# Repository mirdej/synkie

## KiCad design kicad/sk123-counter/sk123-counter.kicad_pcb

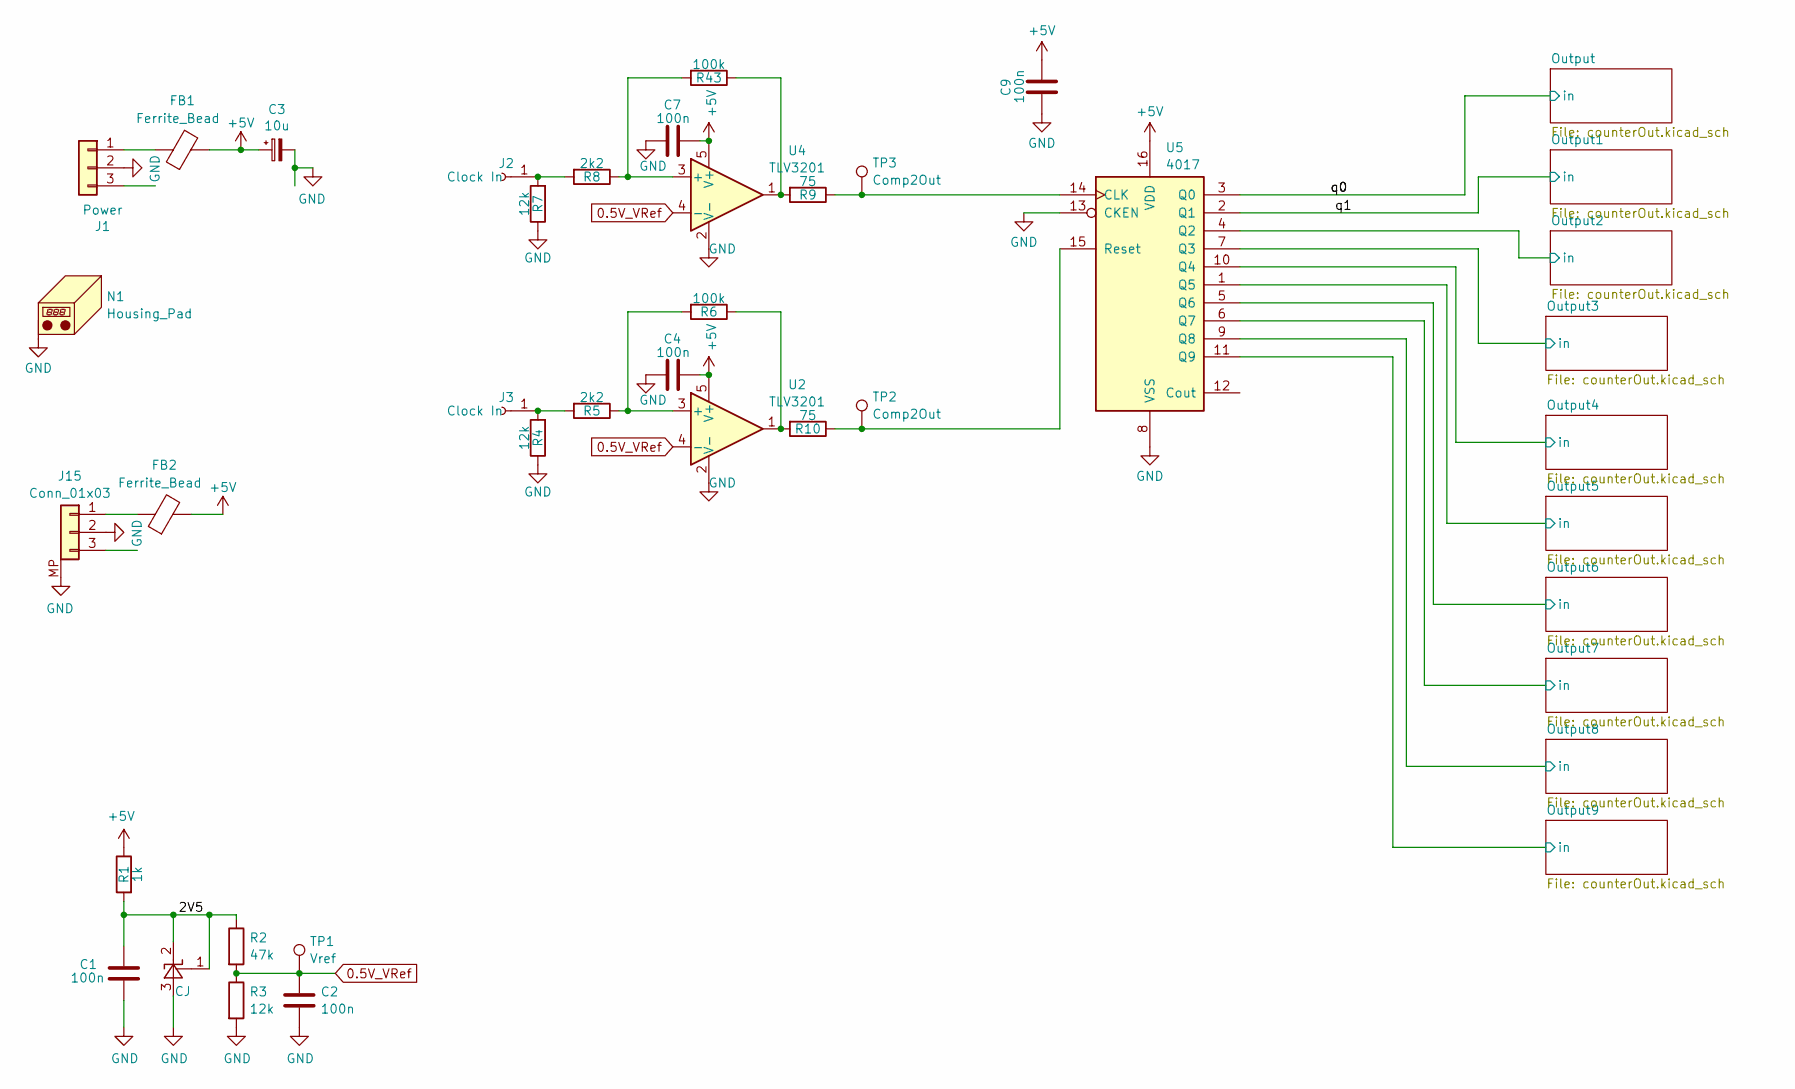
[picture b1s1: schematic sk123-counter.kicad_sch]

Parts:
C1, C2, C4, C7, C9: 100n; C_0603_1608Metric; LCSC C14663
C3: 10u; C_0805_2012Metric; LCSC C15850
FB1, FB2: Ferrite_Bead; L_0805_2012Metric; LCSC C1017
J1: Power; Molex_KK-254_AE-6410-03A_1x03_P2.54mm_Vertical_SMD
J2, J3: Clock In; Banana2mm-Löthülse
J15: Conn_01x03; Molex_PicoBlade_53398-0371_1x03-1MP_P1.25mm_Vertical; LCSC C293633
N1: Housing_Pad; Frontplate_20mm
R1: 1k; R_0603_1608Metric; LCSC C21190
R2: 47k; R_0603_1608Metric; LCSC C25819
R3, R4, R7: 12k; R_0603_1608Metric; LCSC C22790
R5, R8: 2k2; R_0603_1608Metric; LCSC C4190
R6, R43: 100k; R_0603_1608Metric; LCSC C25803
R9, R10: 75; R_0603_1608Metric; LCSC C4275
TP1: Vref; TestPoint_Pad_D1.0mm
TP2, TP3: Comp2Out; TestPoint_Pad_D1.0mm
U1: CJ; SOT-23; LCSC C3113
U2, U4: TLV3201; SOT-23-5; LCSC C105188
U5: 4017; SO-16_3.9x9.9mm_P1.27mm; LCSC C546952

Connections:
0.5V_VRef: C2.1, R2.2, R3.1, TP1.1 (1_1), U2.4 (-), U4.4 (-)
+5V: C3.1, C4.2, C7.2, C9.2, FB1.2, FB2.2, R1.1, U2.5 (V+), U4.5 (V+), U5.16 (VDD); also elsewhere on the board
/2V5: C1.1, R1.2, R2.1, U1.1 (R), U1.2 (K)
/Output2/in: U5.4 (Q2); also elsewhere on the board
/Output3/in: U5.7 (Q3); also elsewhere on the board
/Output4/in: U5.10 (Q4); also elsewhere on the board
/Output5/in: U5.1 (Q5); also elsewhere on the board
/Output6/in: U5.5 (Q6); also elsewhere on the board
/Output7/in: U5.6 (Q7); also elsewhere on the board
/Output8/in: U5.9 (Q8); also elsewhere on the board
/Output9/in: U5.11 (Q9); also elsewhere on the board
/Output/in: U5.3 (Q0); also elsewhere on the board
/q1: U5.2 (Q1); also elsewhere on the board
GND: C1.2, C2.2, C3.2, C4.1, C7.1, C9.1, J1.2, J15.2, J15.MP, N1.1 (PAD_1), R3.2, R4.1, R7.1, U1.3 (A), U2.2 (V-), U4.2 (V-), U5.8 (VSS), U5.13 (CKEN); also elsewhere on the board
unnamed: FB1.1, J1.1
unnamed: J2.1 (Pin_1_1), R7.2, R8.2
unnamed: J3.1 (Pin_1_1), R4.2, R5.2
unnamed: FB2.1, J15.1
unnamed: R6.1, R10.2, U2.1
unnamed: R9.2, R43.1, U4.1
unnamed: R5.1, R6.2, U2.3 (+)
unnamed: R8.1, R43.2, U4.3 (+)
unnamed: R9.1, TP3.1 (1_1), U5.14 (CLK)
unnamed: R10.1, TP2.1 (1_1), U5.15 (Reset)

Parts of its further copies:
R18: 2k2; R_0603_1608Metric; LCSC C4190

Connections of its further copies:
unnamed 15: R18.1; also elsewhere on the board
unnamed 41: R18.2; also elsewhere on the board

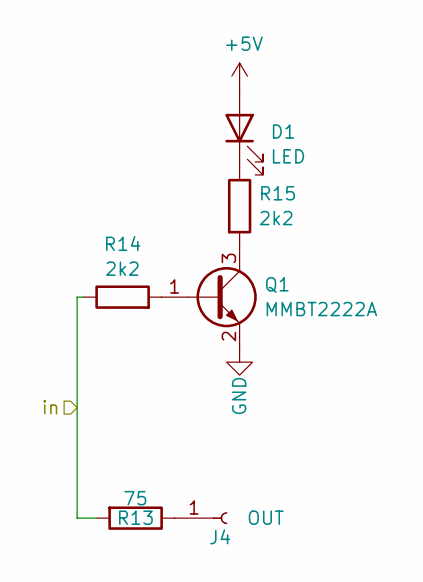
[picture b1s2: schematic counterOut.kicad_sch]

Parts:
D1: LED; LED_1206_3216Metric_ReverseMount_Hole1.8x2.4mm; LCSC C125108
J4: OUT; Banana2mm-Löthülse
Q1: MMBT2222A; SOT-23; LCSC C8512
R13: 75; R_0603_1608Metric; LCSC C4275
R14, R15: 2k2; R_0603_1608Metric; LCSC C4190

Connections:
+5V: D1.2 (A); also elsewhere on the board
/Output/in: R13.2, R14.1; also elsewhere on the board
GND: Q1.2 (E); also elsewhere on the board
unnamed: D1.1 (K), R15.1
unnamed: J4.1 (Pin_1_1), R13.1
unnamed: Q1.1 (B), R14.2
unnamed: Q1.3 (C), R15.2

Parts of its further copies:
D2, D3, D4, D5, D6, D7, D8, D9, D10: LED; LED_1206_3216Metric_ReverseMount_Hole1.8x2.4mm; LCSC C125108
J5, J6, J7, J8, J9, J10, J11, J12, J13: OUT; Banana2mm-Löthülse
Q2, Q3, Q4, Q5, Q6, Q7, Q8, Q9, Q10: MMBT2222A; SOT-23; LCSC C8512
R16, R18, R19, R21, R22, R24, R25, R27, R28, R30, R31, R33, R34, R36, R37, R39, R40, R42: 2k2; R_0603_1608Metric; LCSC C4190
R17, R20, R23, R26, R29, R32, R35, R38, R41: 75; R_0603_1608Metric; LCSC C4275

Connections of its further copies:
+5V: D2.2 (A), D3.2 (A), D4.2 (A), D5.2 (A), D6.2 (A), D7.2 (A), D8.2 (A), D9.2 (A), D10.2 (A); also elsewhere on the board
/Output2/in: R22.1, R23.2; also elsewhere on the board
/Output3/in: R19.1, R20.2; also elsewhere on the board
/Output4/in: R25.1, R26.2; also elsewhere on the board
/Output5/in: R28.1, R29.2; also elsewhere on the board
/Output6/in: R31.1, R32.2; also elsewhere on the board
/Output7/in: R34.1, R35.2; also elsewhere on the board
/Output8/in: R37.1, R38.2; also elsewhere on the board
/Output9/in: R40.1, R41.2; also elsewhere on the board
/q1: R16.1, R17.2; also elsewhere on the board
GND: Q2.2 (E), Q3.2 (E), Q4.2 (E), Q5.2 (E), Q6.2 (E), Q7.2 (E), Q8.2 (E), Q9.2 (E), Q10.2 (E); also elsewhere on the board
unnamed: D2.1 (K), R18.1
unnamed: D3.1 (K), R21.1
unnamed: D4.1 (K), R24.1
unnamed: D5.1 (K), R27.1
unnamed: D6.1 (K), R30.1
unnamed: D7.1 (K), R33.1
unnamed: D8.1 (K), R36.1
unnamed: D9.1 (K), R39.1
unnamed: D10.1 (K), R42.1
unnamed: J5.1 (Pin_1_1), R17.1
unnamed: J6.1 (Pin_1_1), R20.1
unnamed: J7.1 (Pin_1_1), R23.1
unnamed: J8.1 (Pin_1_1), R26.1
unnamed: J9.1 (Pin_1_1), R29.1
unnamed: J10.1 (Pin_1_1), R32.1
unnamed: J11.1 (Pin_1_1), R35.1
unnamed: J12.1 (Pin_1_1), R38.1
unnamed: J13.1 (Pin_1_1), R41.1
unnamed: Q2.1 (B), R16.2
unnamed: Q2.3 (C), R18.2
unnamed: Q3.1 (B), R19.2
unnamed: Q3.3 (C), R21.2
unnamed: Q4.1 (B), R22.2
unnamed: Q4.3 (C), R24.2
unnamed: Q5.1 (B), R25.2
unnamed: Q5.3 (C), R27.2
unnamed: Q6.1 (B), R28.2
unnamed: Q6.3 (C), R30.2
unnamed: Q7.1 (B), R31.2
unnamed: Q7.3 (C), R33.2
unnamed: Q8.1 (B), R34.2
unnamed: Q8.3 (C), R36.2
unnamed: Q9.1 (B), R37.2
unnamed: Q9.3 (C), R39.2
unnamed: Q10.1 (B), R40.2
unnamed: Q10.3 (C), R42.2

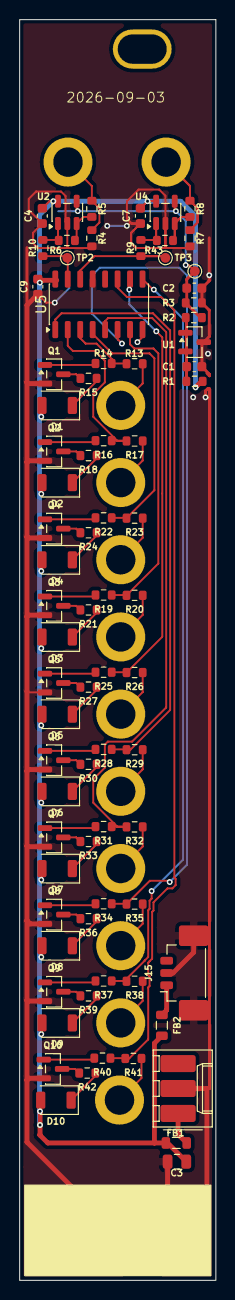
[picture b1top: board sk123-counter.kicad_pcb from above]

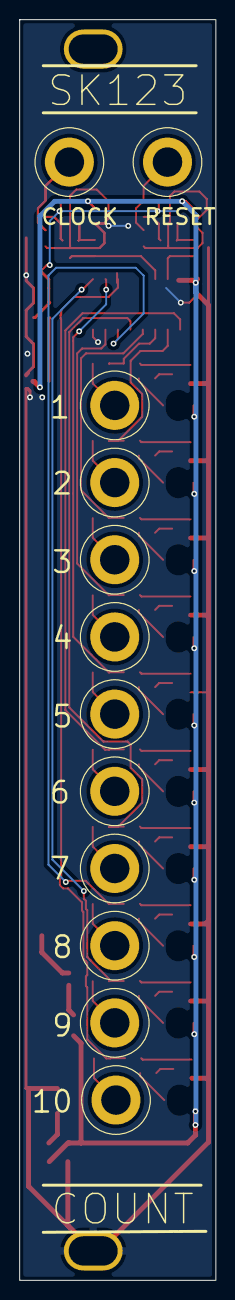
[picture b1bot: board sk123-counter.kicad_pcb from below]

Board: 2 copper layers, 20.0 x 128.5 mm, 91 parts (13 on the bottom side), 64 nets.

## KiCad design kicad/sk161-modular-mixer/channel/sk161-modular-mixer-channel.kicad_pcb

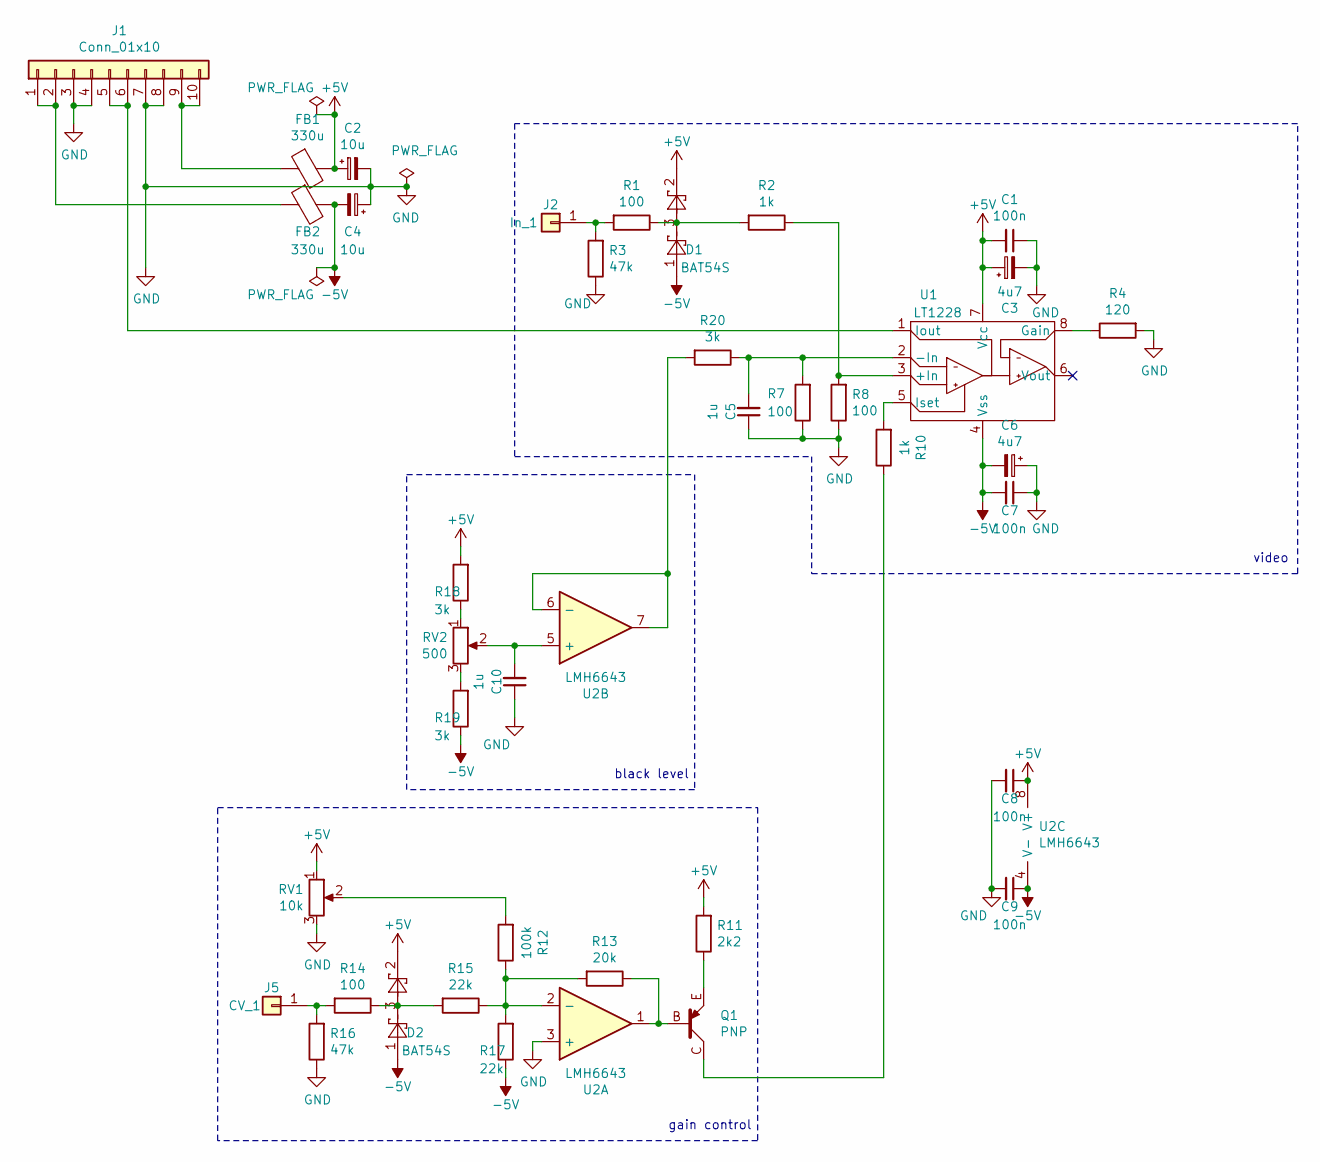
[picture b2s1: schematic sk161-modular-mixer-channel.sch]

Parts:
C1, C7, C8, C9: 100n; C_0603_1608Metric_Pad1.05x0.95mm_HandSolder
C2, C4: 10u; CP_EIA-3528-21_Kemet-B_Pad1.50x2.35mm_HandSolder
C3, C6: 4u7; CP_EIA-3528-21_Kemet-B_Pad1.50x2.35mm_HandSolder
C5, C10: 1u; C_0603_1608Metric_Pad1.05x0.95mm_HandSolder
D1, D2: BAT54S; SOT-23
FB1, FB2: 330u; L_0805_2012Metric_Pad1.15x1.40mm_HandSolder
J1: Conn_01x10; IDC-Header_2x05_P2.54mm_Vertical
J2: In_1; Solderpad_1mm
J5: CV_1; Solderpad_1mm
Q1: PNP; SOT-23_BEC
R1, R7, R8, R14: 100; R_0805_2012Metric_Pad1.15x1.40mm_HandSolder
R2, R10: 1k; R_0805_2012Metric_Pad1.15x1.40mm_HandSolder
R3, R16: 47k; R_0805_2012Metric_Pad1.15x1.40mm_HandSolder
R4: 120; R_0805_2012Metric_Pad1.15x1.40mm_HandSolder
R11: 2k2; R_0805_2012Metric_Pad1.15x1.40mm_HandSolder
R12: 100k; R_0805_2012Metric_Pad1.15x1.40mm_HandSolder
R13: 20k; R_0805_2012Metric_Pad1.15x1.40mm_HandSolder
R15, R17: 22k; R_0805_2012Metric_Pad1.15x1.40mm_HandSolder
R18, R19, R20: 3k; R_0805_2012Metric_Pad1.15x1.40mm_HandSolder
RV1: 10k; Potentiometer_Alps_RS6011xP_Slide
RV2: 500; Potentiometer_Bourns_3296Y_Vertical
U1: LT1228; SOIC-8_3.9x4.9mm_P1.27mm
U2: LMH6643; SOIC-8_3.9x4.9mm_P1.27mm

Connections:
+5V: C1.2, C2.1, C3.1, C8.1, D1.2, D2.2, FB1.2, R11.2, R18.2, RV1.1, U1.7 (Vcc), U2.8 (V+)
-5V: C4.2, C6.2, C7.2, C9.1, D1.1, D2.1, FB2.2, R17.1, R19.1, U1.4 (Vss), U2.4 (V-)
GND: C1.1, C2.2, C3.2, C4.1, C5.1, C6.1, C7.1, C8.2, C9.2, C10.1, J1.3, J1.4, J1.7, J1.8, R3.1, R4.2, R7.1, R8.1, R16.1, RV1.3, RV1.4, RV1.5, U2.3 (+)
unnamed: C5.2, R7.2, R20.1, U1.2 (-In)
unnamed: C10.2, RV2.2, U2.5 (+)
unnamed: D1.3, R1.1, R2.2
unnamed: D2.3, R14.1, R15.2
unnamed: FB1.1, J1.9, J1.10
unnamed: FB2.1, J1.1, J1.2
unnamed: J1.5, J1.6, U1.1 (Iout)
unnamed: J2.1, R1.2, R3.2
unnamed: J5.1, R14.2, R16.2
unnamed: Q1.B, R13.1, U2.1
unnamed: Q1.C, R10.1
unnamed: Q1.E, R11.1
unnamed: R2.1, R8.2, U1.3 (+In)
unnamed: R4.1, U1.8 (Gain)
unnamed: R10.2, U1.5 (Iset)
unnamed: R12.1, R13.2, R15.1, R17.2, U2.2 (-)
unnamed: R12.2, RV1.2
unnamed: R18.1, RV2.1
unnamed: R19.2, RV2.3
unnamed: R20.2, U2.6 (-), U2.7

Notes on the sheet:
black level
gain control
video

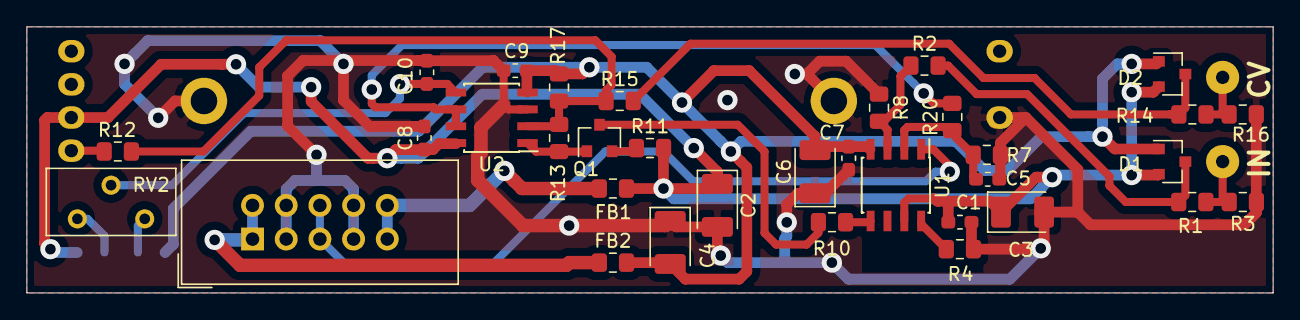
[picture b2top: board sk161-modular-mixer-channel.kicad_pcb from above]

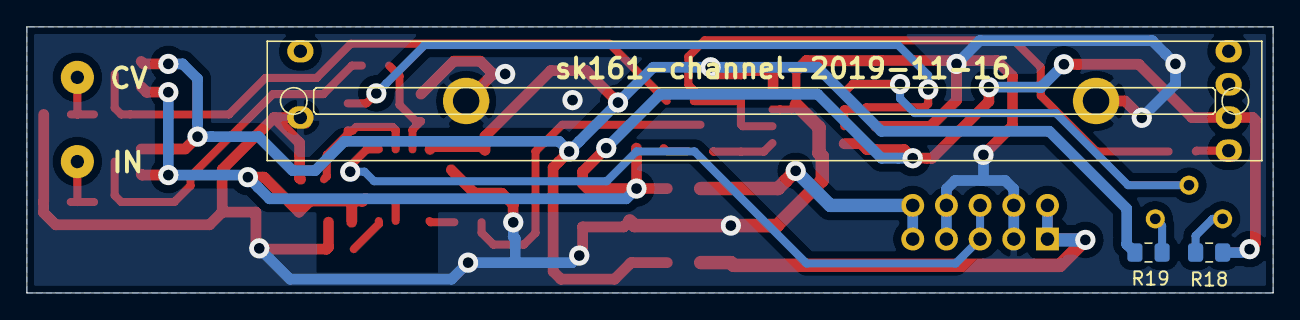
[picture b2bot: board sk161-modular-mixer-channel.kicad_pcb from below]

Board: 2 copper layers, 94.0 x 20.1 mm, 39 parts (3 on the bottom side), 23 nets.

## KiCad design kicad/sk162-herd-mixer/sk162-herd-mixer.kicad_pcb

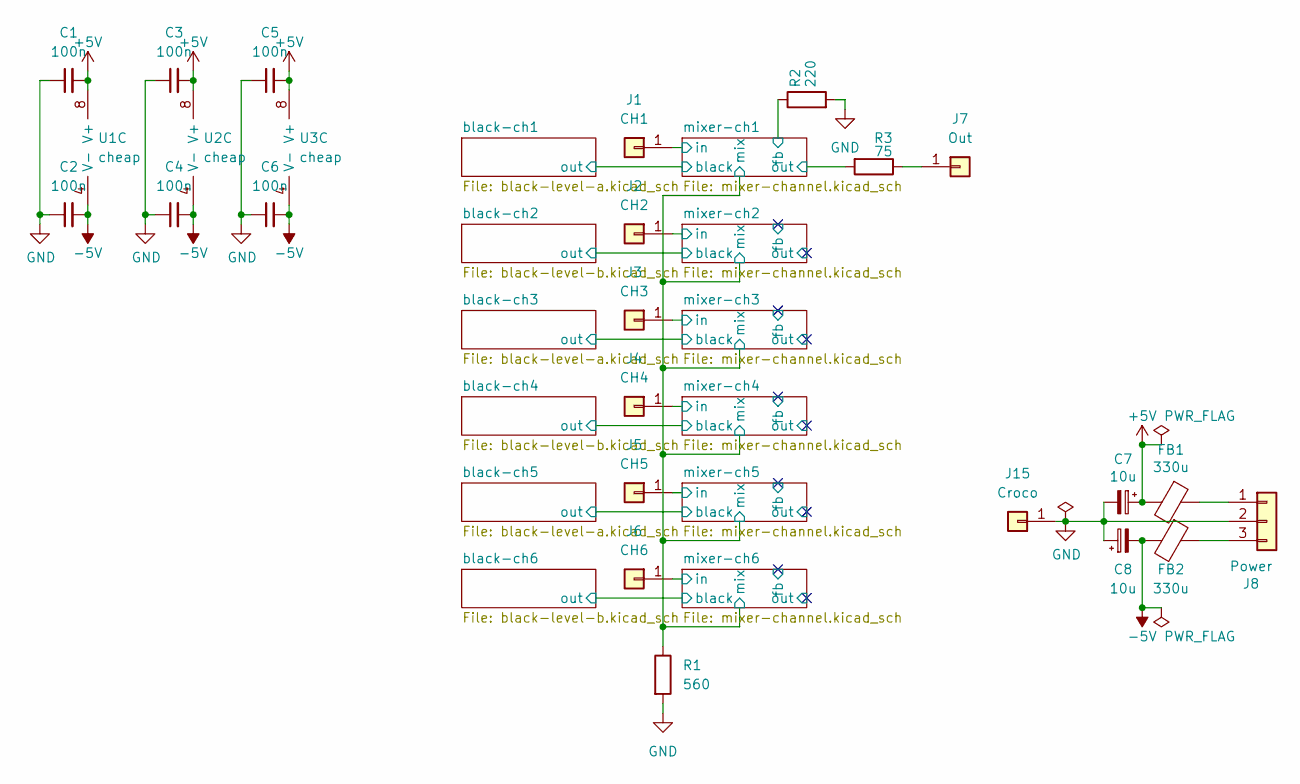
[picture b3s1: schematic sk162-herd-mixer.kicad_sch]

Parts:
C1, C2, C3, C4, C5, C6: 100n; C_0603_1608Metric_Pad1.05x0.95mm_HandSolder
C7, C8: 10u; C_0805_2012Metric_Pad1.15x1.40mm_HandSolder
FB1, FB2: 330u; L_0805_2012Metric_Pad1.15x1.40mm_HandSolder
J1: CH1; Solderpad-SYNKIEPAD-2mm
J2: CH2; Solderpad-SYNKIEPAD-2mm
J3: CH3; Solderpad-SYNKIEPAD-2mm
J4: CH4; Solderpad-SYNKIEPAD-2mm
J5: CH5; Solderpad-SYNKIEPAD-2mm
J6: CH6; Solderpad-SYNKIEPAD-2mm
J7: Out; Solderpad-SYNKIEPAD-2mm
J8: Power; Molex_KK-254_AE-6410-03A_1x03_P2.54mm_Vertical
J15: Croco; CrocodileGroundPad
R1: 560; R_0805_2012Metric_Pad1.15x1.40mm_HandSolder
R2: 220; R_0805_2012Metric_Pad1.15x1.40mm_HandSolder
R3: 75; R_0805_2012Metric_Pad1.15x1.40mm_HandSolder
U1, U2, U3: cheap; SOIC-8_3.9x4.9mm_P1.27mm

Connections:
+5V: C1.2, C3.2, C5.2, C7.1, FB1.2, U1.8 (V+), U2.8 (V+), U3.8 (V+); also elsewhere on the board
-5V: C2.2, C4.2, C6.2, C8.2, FB2.2, U1.4 (V-), U2.4 (V-), U3.4 (V-); also elsewhere on the board
/mixer-ch1/fb: R2.1; also elsewhere on the board
/mixer-ch1/in: J1.1; also elsewhere on the board
/mixer-ch1/mix: R1.1; also elsewhere on the board
/mixer-ch1/out: R3.2; also elsewhere on the board
/mixer-ch2/in: J2.1; also elsewhere on the board
/mixer-ch3/in: J3.1; also elsewhere on the board
/mixer-ch4/in: J4.1; also elsewhere on the board
/mixer-ch5/in: J5.1; also elsewhere on the board
/mixer-ch6/in: J6.1; also elsewhere on the board
GND: C1.1, C2.1, C3.1, C4.1, C5.1, C6.1, C7.2, C8.1, J8.2, J15.1, R1.2, R2.2; also elsewhere on the board
unnamed: J7.1, R3.1
unnamed: FB1.1, J8.1
unnamed: FB2.1, J8.3

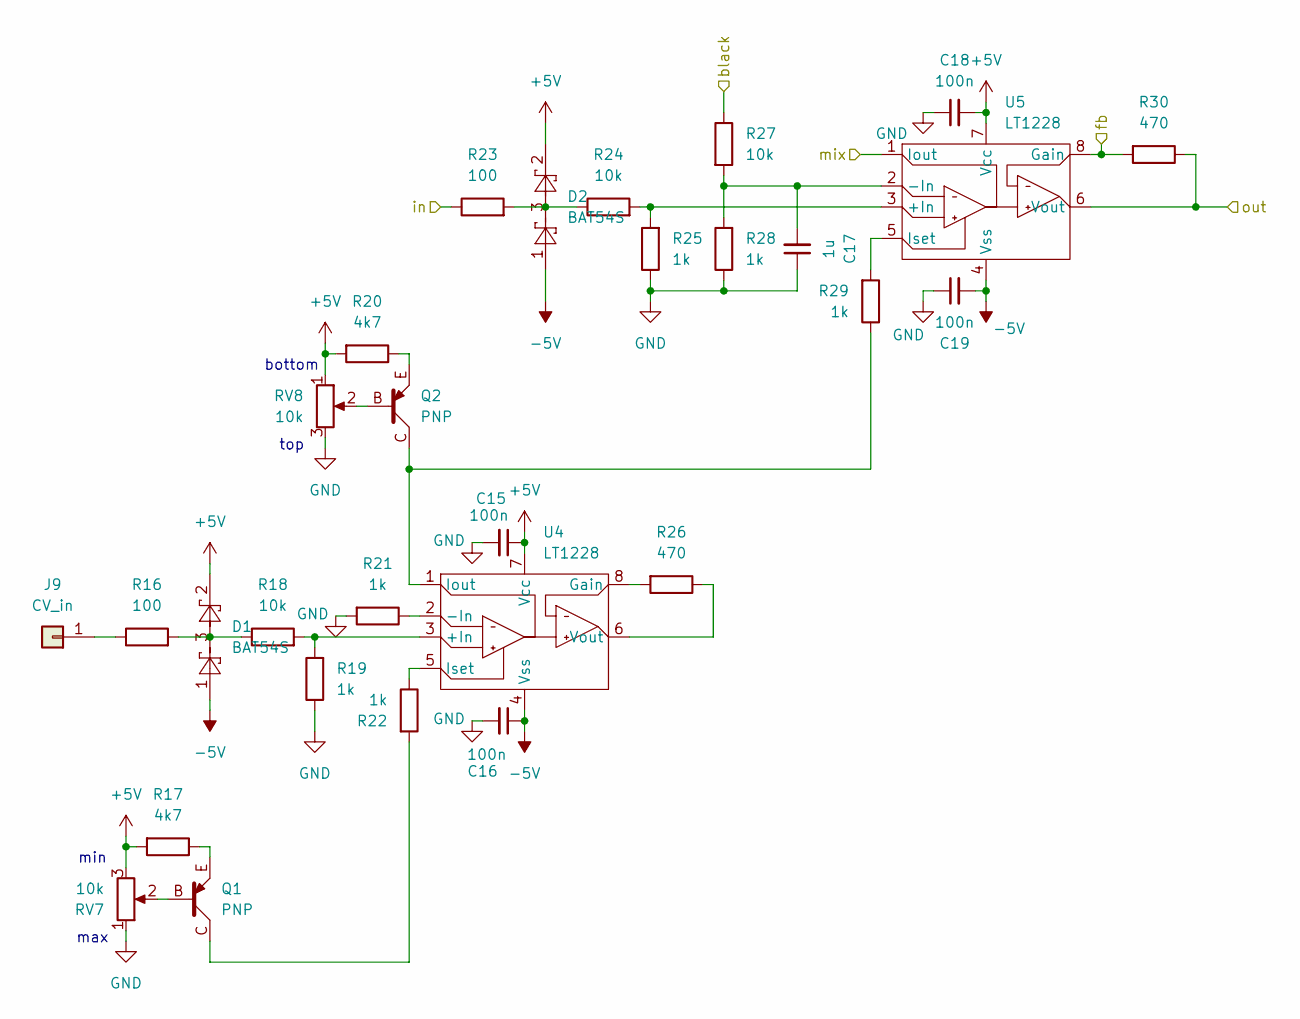
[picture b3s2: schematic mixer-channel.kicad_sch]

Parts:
C15, C16, C18, C19: 100n; C_0603_1608Metric_Pad1.05x0.95mm_HandSolder
C17: 1u; C_0603_1608Metric_Pad1.05x0.95mm_HandSolder
D1, D2: BAT54S; SOT-23
J9: CV_in; Solderpad-SYNKIEPAD-2mm
Q1, Q2: PNP; SOT-23_BEC
R16, R23: 100; R_0805_2012Metric_Pad1.15x1.40mm_HandSolder
R17, R20: 4k7; R_0805_2012Metric_Pad1.15x1.40mm_HandSolder
R18, R24, R27: 10k; R_0805_2012Metric_Pad1.15x1.40mm_HandSolder
R19, R21, R22, R25, R28, R29: 1k; R_0805_2012Metric_Pad1.15x1.40mm_HandSolder
R26, R30: 470; R_0805_2012Metric_Pad1.15x1.40mm_HandSolder
RV7: 10k; Potentiometer_Alps_RK09K_Single_Vertical
RV8: 10k; Potentiometer_Alps_RS6011xP_Slide
U4, U5: LT1228; SOIC-8_3.9x4.9mm_P1.27mm

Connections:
+5V: C15.1, C18.2, D1.2, D2.2, R17.2, R20.2, RV7.3, RV8.1, U4.7 (Vcc), U5.7 (Vcc); also elsewhere on the board
-5V: C16.1, C19.2, D1.1, D2.1, U4.4 (Vss), U5.4 (Vss); also elsewhere on the board
/black-ch1/out: R27.1; also elsewhere on the board
/mixer-ch1/fb: R30.2, U5.8 (Gain); also elsewhere on the board
/mixer-ch1/in: R23.1; also elsewhere on the board
/mixer-ch1/mix: U5.1 (Iout); also elsewhere on the board
/mixer-ch1/out: R30.1, U5.6 (Vout); also elsewhere on the board
GND: C15.2, C16.2, C17.1, C18.1, C19.1, R19.1, R21.2, R25.1, R28.1, RV7.1, RV8.3; also elsewhere on the board
unnamed: D1.3, R16.2, R18.1
unnamed: D2.3, R23.2, R24.1
unnamed: J9.1, R16.1
unnamed: Q1.B, RV7.2
unnamed: Q1.C, R22.2
unnamed: Q1.E, R17.1
unnamed: Q2.B, RV8.2
unnamed: Q2.E, R20.1
unnamed: R18.2, R19.2, U4.3 (+In)
unnamed: R21.1, U4.2 (-In)
unnamed: R26.2, U4.8 (Gain)
unnamed: Q2.C, R29.1, U4.1 (Iout)
unnamed: R22.1, U4.5 (Iset)
unnamed: R26.1, U4.6 (Vout)
unnamed: R24.2, R25.2, U5.3 (+In)
unnamed: C17.2, R27.2, R28.2, U5.2 (-In)
unnamed: R29.2, U5.5 (Iset)

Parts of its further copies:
C20, C21, C23, C24, C25, C26, C28, C29, C30, C31, C33, C34, C35, C36, C38, C39, C40, C41, C43, C44: 100n; C_0603_1608Metric_Pad1.05x0.95mm_HandSolder
C22, C27, C32, C37, C42: 1u; C_0603_1608Metric_Pad1.05x0.95mm_HandSolder
D3, D4, D5, D6, D7, D8, D9, D10, D11, D12: BAT54S; SOT-23
J10, J11, J12, J13, J14: CV_in; Solderpad-SYNKIEPAD-2mm
Q3, Q4, Q5, Q6, Q7, Q8, Q9, Q10, Q11, Q12: PNP; SOT-23_BEC
R31, R38, R46, R53, R61, R68, R76, R83, R91, R98: 100; R_0805_2012Metric_Pad1.15x1.40mm_HandSolder
R32, R35, R47, R50, R62, R65, R77, R80, R92, R95: 4k7; R_0805_2012Metric_Pad1.15x1.40mm_HandSolder
R33, R39, R42, R48, R54, R57, R63, R69, R72, R78, R84, R87, R93, R99, R102: 10k; R_0805_2012Metric_Pad1.15x1.40mm_HandSolder
R34, R36, R37, R40, R43, R44, R49, R51, R52, R55, R58, R59, R64, R66, R67, R70, R73, R74, R79, R81, R82, R85, R88, R89, R94, R96, R97, R100, R103, R104: 1k; R_0805_2012Metric_Pad1.15x1.40mm_HandSolder
R41, R45, R56, R60, R71, R75, R86, R90, R101, R105: 470; R_0805_2012Metric_Pad1.15x1.40mm_HandSolder
RV9, RV11, RV13, RV15, RV17: 10k; Potentiometer_Alps_RK09K_Single_Vertical
RV10, RV12, RV14, RV16, RV18: 10k; Potentiometer_Alps_RS6011xP_Slide
U6, U7, U8, U9, U10, U11, U12, U13, U14, U15: LT1228; SOIC-8_3.9x4.9mm_P1.27mm

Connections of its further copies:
+5V: C20.1, C23.2, C25.1, C28.2, C30.1, C33.2, C35.1, C38.2, C40.1, C43.2, D3.2, D4.2, D5.2, D6.2, D7.2, D8.2, D9.2, D10.2, D11.2, D12.2, R32.2, R35.2, R47.2, R50.2, R62.2, R65.2, R77.2, R80.2, R92.2, R95.2, RV9.3, RV10.1, RV11.3, RV12.1, RV13.3, RV14.1, RV15.3, RV16.1, RV17.3, RV18.1, U6.7 (Vcc), U7.7 (Vcc), U8.7 (Vcc), U9.7 (Vcc), U10.7 (Vcc), U11.7 (Vcc), U12.7 (Vcc), U13.7 (Vcc), U14.7 (Vcc), U15.7 (Vcc); also elsewhere on the board
-5V: C21.1, C24.2, C26.1, C29.2, C31.1, C34.2, C36.1, C39.2, C41.1, C44.2, D3.1, D4.1, D5.1, D6.1, D7.1, D8.1, D9.1, D10.1, D11.1, D12.1, U6.4 (Vss), U7.4 (Vss), U8.4 (Vss), U9.4 (Vss), U10.4 (Vss), U11.4 (Vss), U12.4 (Vss), U13.4 (Vss), U14.4 (Vss), U15.4 (Vss); also elsewhere on the board
/black-ch2/out: R42.1; also elsewhere on the board
/black-ch3/out: R57.1; also elsewhere on the board
/black-ch4/out: R72.1; also elsewhere on the board
/black-ch5/out: R87.1; also elsewhere on the board
/black-ch6/out: R102.1; also elsewhere on the board
/mixer-ch1/mix: U7.1 (Iout), U9.1 (Iout), U11.1 (Iout), U13.1 (Iout), U15.1 (Iout); also elsewhere on the board
/mixer-ch2/fb: R45.2, U7.8 (Gain)
/mixer-ch2/in: R38.1; also elsewhere on the board
/mixer-ch2/out: R45.1, U7.6 (Vout)
/mixer-ch3/fb: R60.2, U9.8 (Gain)
/mixer-ch3/in: R53.1; also elsewhere on the board
/mixer-ch3/out: R60.1, U9.6 (Vout)
/mixer-ch4/fb: R75.2, U11.8 (Gain)
/mixer-ch4/in: R68.1; also elsewhere on the board
/mixer-ch4/out: R75.1, U11.6 (Vout)
/mixer-ch5/fb: R90.2, U13.8 (Gain)
/mixer-ch5/in: R83.1; also elsewhere on the board
/mixer-ch5/out: R90.1, U13.6 (Vout)
/mixer-ch6/fb: R105.2, U15.8 (Gain)
/mixer-ch6/in: R98.1; also elsewhere on the board
/mixer-ch6/out: R105.1, U15.6 (Vout)
GND: C20.2, C21.2, C22.1, C23.1, C24.1, C25.2, C26.2, C27.1, C28.1, C29.1, C30.2, C31.2, C32.1, C33.1, C34.1, C35.2, C36.2, C37.1, C38.1, C39.1, C40.2, C41.2, C42.1, C43.1, C44.1, R34.1, R36.2, R40.1, R43.1, R49.1, R51.2, R55.1, R58.1, R64.1, R66.2, R70.1, R73.1, R79.1, R81.2, R85.1, R88.1, R94.1, R96.2, R100.1, R103.1, RV9.1, RV10.3, RV11.1, RV12.3, RV13.1, RV14.3, RV15.1, RV16.3, RV17.1, RV18.3; also elsewhere on the board
unnamed: D3.3, R31.2, R33.1
unnamed: D4.3, R38.2, R39.1
unnamed: D5.3, R46.2, R48.1
unnamed: D6.3, R53.2, R54.1
unnamed: D7.3, R61.2, R63.1
unnamed: D8.3, R68.2, R69.1
unnamed: D9.3, R76.2, R78.1
unnamed: D10.3, R83.2, R84.1
unnamed: D11.3, R91.2, R93.1
unnamed: D12.3, R98.2, R99.1
unnamed: J10.1, R31.1
unnamed: J11.1, R46.1
unnamed: J12.1, R61.1
unnamed: J13.1, R76.1
unnamed: J14.1, R91.1
unnamed: Q3.B, RV9.2
unnamed: Q3.C, R37.2
unnamed: Q3.E, R32.1
unnamed: Q4.B, RV10.2
unnamed: Q4.E, R35.1
unnamed: Q5.B, RV11.2
unnamed: Q5.C, R52.2
unnamed: Q5.E, R47.1
unnamed: Q6.B, RV12.2
unnamed: Q6.E, R50.1
unnamed: Q7.B, RV13.2
unnamed: Q7.C, R67.2
unnamed: Q7.E, R62.1
unnamed: Q8.B, RV14.2
unnamed: Q8.E, R65.1
unnamed: Q9.B, RV15.2
unnamed: Q9.C, R82.2
unnamed: Q9.E, R77.1
unnamed: Q10.B, RV16.2
unnamed: Q10.E, R80.1
unnamed: Q11.B, RV17.2
unnamed: Q11.C, R97.2
unnamed: Q11.E, R92.1
unnamed: Q12.B, RV18.2
unnamed: Q12.E, R95.1
unnamed: R33.2, R34.2, U6.3 (+In)
unnamed: R36.1, U6.2 (-In)
unnamed: R41.2, U6.8 (Gain)
unnamed: Q4.C, R44.1, U6.1 (Iout)
unnamed: R37.1, U6.5 (Iset)
unnamed: R41.1, U6.6 (Vout)
unnamed: R39.2, R40.2, U7.3 (+In)
unnamed: C22.2, R42.2, R43.2, U7.2 (-In)
unnamed: R44.2, U7.5 (Iset)
unnamed: R48.2, R49.2, U8.3 (+In)
unnamed: R51.1, U8.2 (-In)
unnamed: R56.2, U8.8 (Gain)
unnamed: Q6.C, R59.1, U8.1 (Iout)
unnamed: R52.1, U8.5 (Iset)
unnamed: R56.1, U8.6 (Vout)
unnamed: R54.2, R55.2, U9.3 (+In)
unnamed: C27.2, R57.2, R58.2, U9.2 (-In)
unnamed: R59.2, U9.5 (Iset)
unnamed: R63.2, R64.2, U10.3 (+In)
unnamed: R66.1, U10.2 (-In)
unnamed: R71.2, U10.8 (Gain)
unnamed: Q8.C, R74.1, U10.1 (Iout)
unnamed: R67.1, U10.5 (Iset)
unnamed: R71.1, U10.6 (Vout)
unnamed: R69.2, R70.2, U11.3 (+In)
unnamed: C32.2, R72.2, R73.2, U11.2 (-In)
unnamed: R74.2, U11.5 (Iset)
unnamed: R78.2, R79.2, U12.3 (+In)
unnamed: R81.1, U12.2 (-In)
unnamed: R86.2, U12.8 (Gain)
unnamed: Q10.C, R89.1, U12.1 (Iout)
unnamed: R82.1, U12.5 (Iset)
unnamed: R86.1, U12.6 (Vout)
unnamed: R84.2, R85.2, U13.3 (+In)
unnamed: C37.2, R87.2, R88.2, U13.2 (-In)
unnamed: R89.2, U13.5 (Iset)
unnamed: R93.2, R94.2, U14.3 (+In)
unnamed: R96.1, U14.2 (-In)
unnamed: R101.2, U14.8 (Gain)
unnamed: Q12.C, R104.1, U14.1 (Iout)
unnamed: R97.1, U14.5 (Iset)
unnamed: R101.1, U14.6 (Vout)
unnamed: R99.2, R100.2, U15.3 (+In)
unnamed: C42.2, R102.2, R103.2, U15.2 (-In)
unnamed: R104.2, U15.5 (Iset)

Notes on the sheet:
max
top
bottom
min

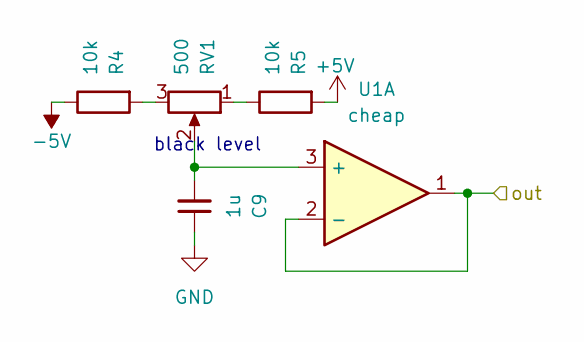
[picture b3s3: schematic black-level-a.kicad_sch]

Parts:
C9: 1u; C_0603_1608Metric_Pad1.05x0.95mm_HandSolder
R4, R5: 10k; R_0805_2012Metric_Pad1.15x1.40mm_HandSolder
RV1: 500; Potentiometer_Bourns_3296Y_Vertical
U1: cheap; SOIC-8_3.9x4.9mm_P1.27mm

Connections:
+5V: R5.2; also elsewhere on the board
-5V: R4.1; also elsewhere on the board
/black-ch1/out: U1.1, U1.2 (-); also elsewhere on the board
GND: C9.1; also elsewhere on the board
unnamed: R4.2, RV1.3
unnamed: R5.1, RV1.1
unnamed: C9.2, RV1.2, U1.3 (+)

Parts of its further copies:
C11, C13: 1u; C_0603_1608Metric_Pad1.05x0.95mm_HandSolder
R8, R9, R12, R13: 10k; R_0805_2012Metric_Pad1.15x1.40mm_HandSolder
RV3, RV5: 500; Potentiometer_Bourns_3296Y_Vertical

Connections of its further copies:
+5V: R9.2, R13.2; also elsewhere on the board
-5V: R8.1, R12.1; also elsewhere on the board
GND: C11.1, C13.1; also elsewhere on the board
unnamed: R8.2, RV3.3
unnamed: R9.1, RV3.1
unnamed: R12.2, RV5.3
unnamed: R13.1, RV5.1
unnamed 93: C11.2, RV3.2; also elsewhere on the board
unnamed 95: C13.2, RV5.2; also elsewhere on the board

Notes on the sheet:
black level

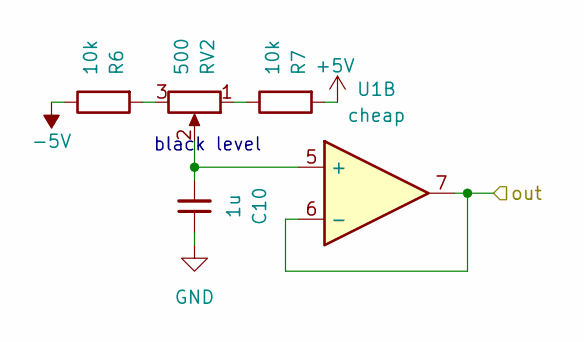
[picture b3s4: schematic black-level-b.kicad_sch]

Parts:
C10: 1u; C_0603_1608Metric_Pad1.05x0.95mm_HandSolder
R6, R7: 10k; R_0805_2012Metric_Pad1.15x1.40mm_HandSolder
RV2: 500; Potentiometer_Bourns_3296Y_Vertical
U1: cheap; SOIC-8_3.9x4.9mm_P1.27mm

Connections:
+5V: R7.2; also elsewhere on the board
-5V: R6.1; also elsewhere on the board
/black-ch2/out: U1.6 (-), U1.7; also elsewhere on the board
GND: C10.1; also elsewhere on the board
unnamed: R6.2, RV2.3
unnamed: R7.1, RV2.1
unnamed: C10.2, RV2.2, U1.5 (+)

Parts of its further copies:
C12, C14: 1u; C_0603_1608Metric_Pad1.05x0.95mm_HandSolder
R10, R11, R14, R15: 10k; R_0805_2012Metric_Pad1.15x1.40mm_HandSolder
RV4, RV6: 500; Potentiometer_Bourns_3296Y_Vertical

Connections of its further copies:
+5V: R11.2, R15.2; also elsewhere on the board
-5V: R10.1, R14.1; also elsewhere on the board
GND: C12.1, C14.1; also elsewhere on the board
unnamed: R10.2, RV4.3
unnamed: R11.1, RV4.1
unnamed: R14.2, RV6.3
unnamed: R15.1, RV6.1
unnamed 94: C12.2, RV4.2; also elsewhere on the board
unnamed 96: C14.2, RV6.2; also elsewhere on the board

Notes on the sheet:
black level

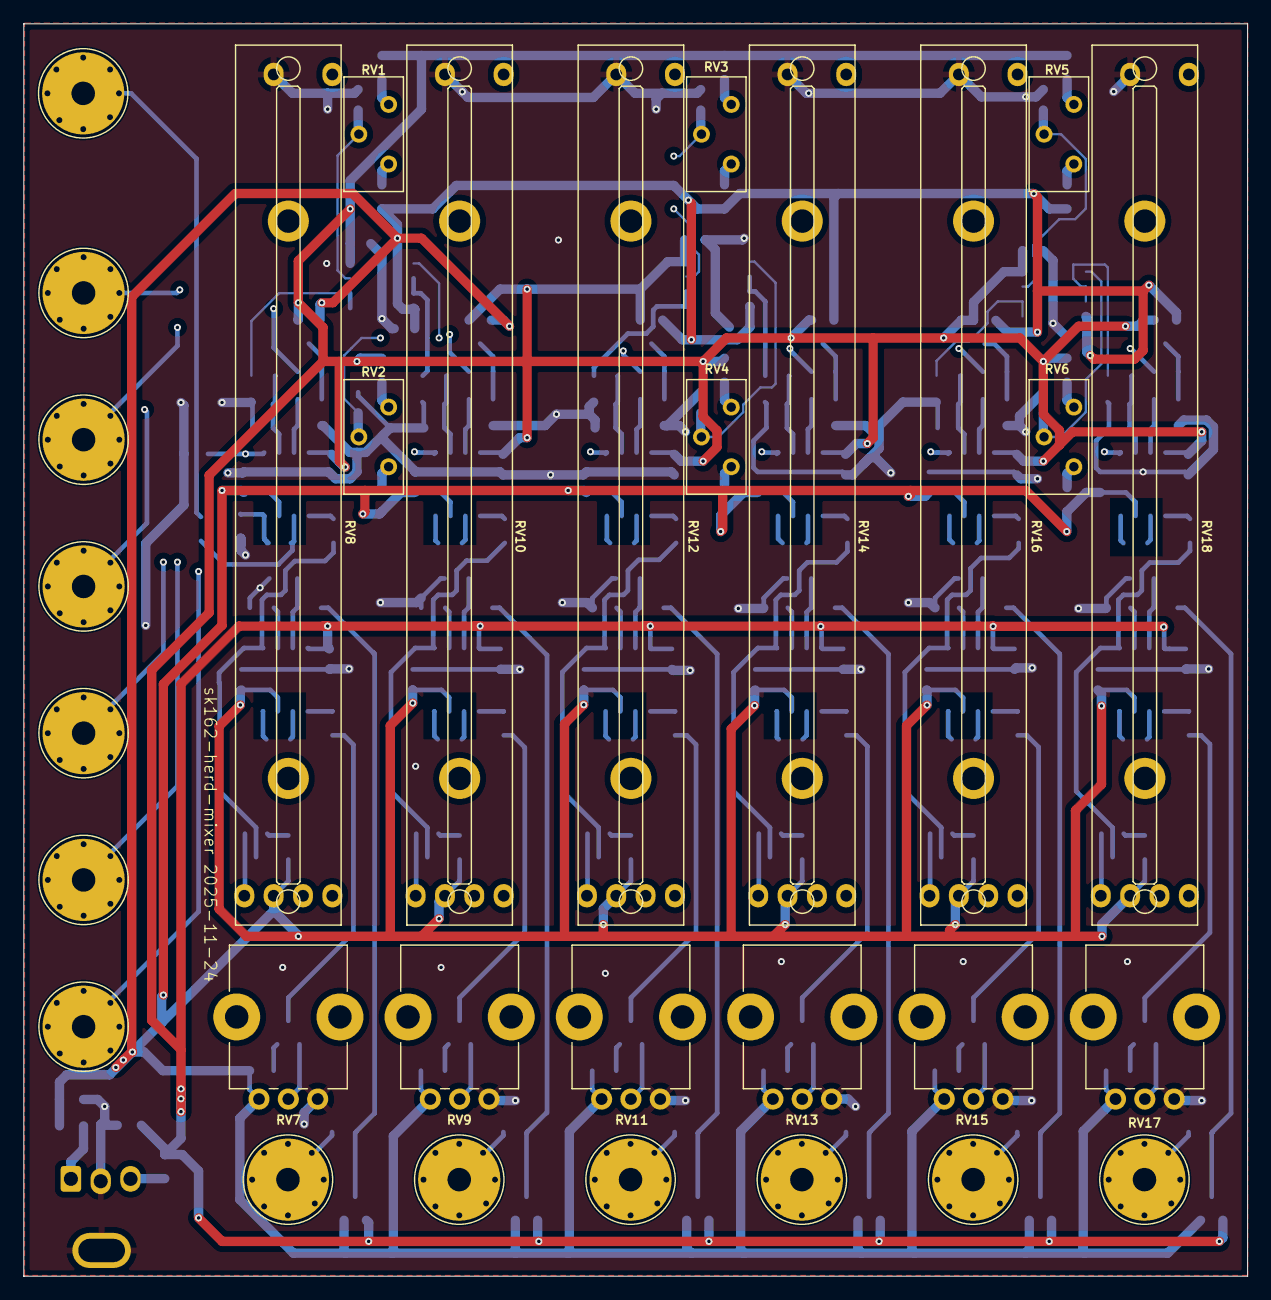
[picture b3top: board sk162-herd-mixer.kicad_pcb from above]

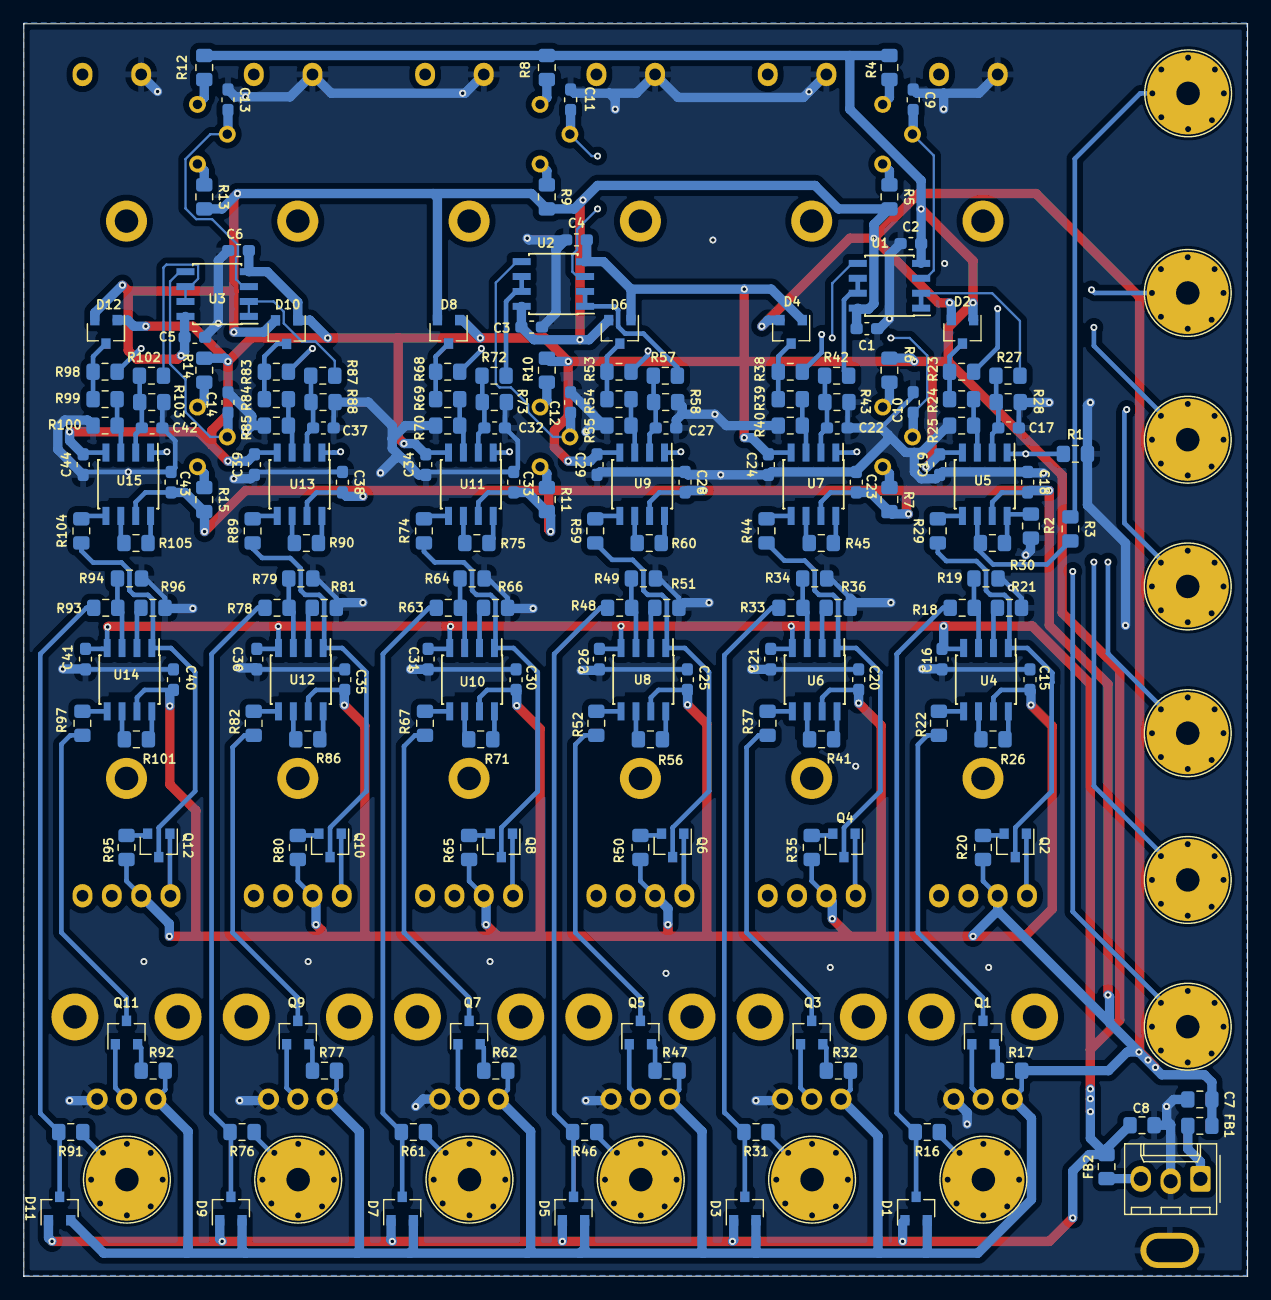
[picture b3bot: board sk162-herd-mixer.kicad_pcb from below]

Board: 4 copper layers, 104.3 x 106.8 mm, 223 parts (191 on the bottom side), 151 nets.
